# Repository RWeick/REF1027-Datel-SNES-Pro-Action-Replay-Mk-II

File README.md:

# REF1027-Datel-SNES-Pro-Action-Replay-Mk-II
Everything necessary to produce the SNES Pro Action Replay Mk II by Datel

PCB Thickness: 1.0 mm

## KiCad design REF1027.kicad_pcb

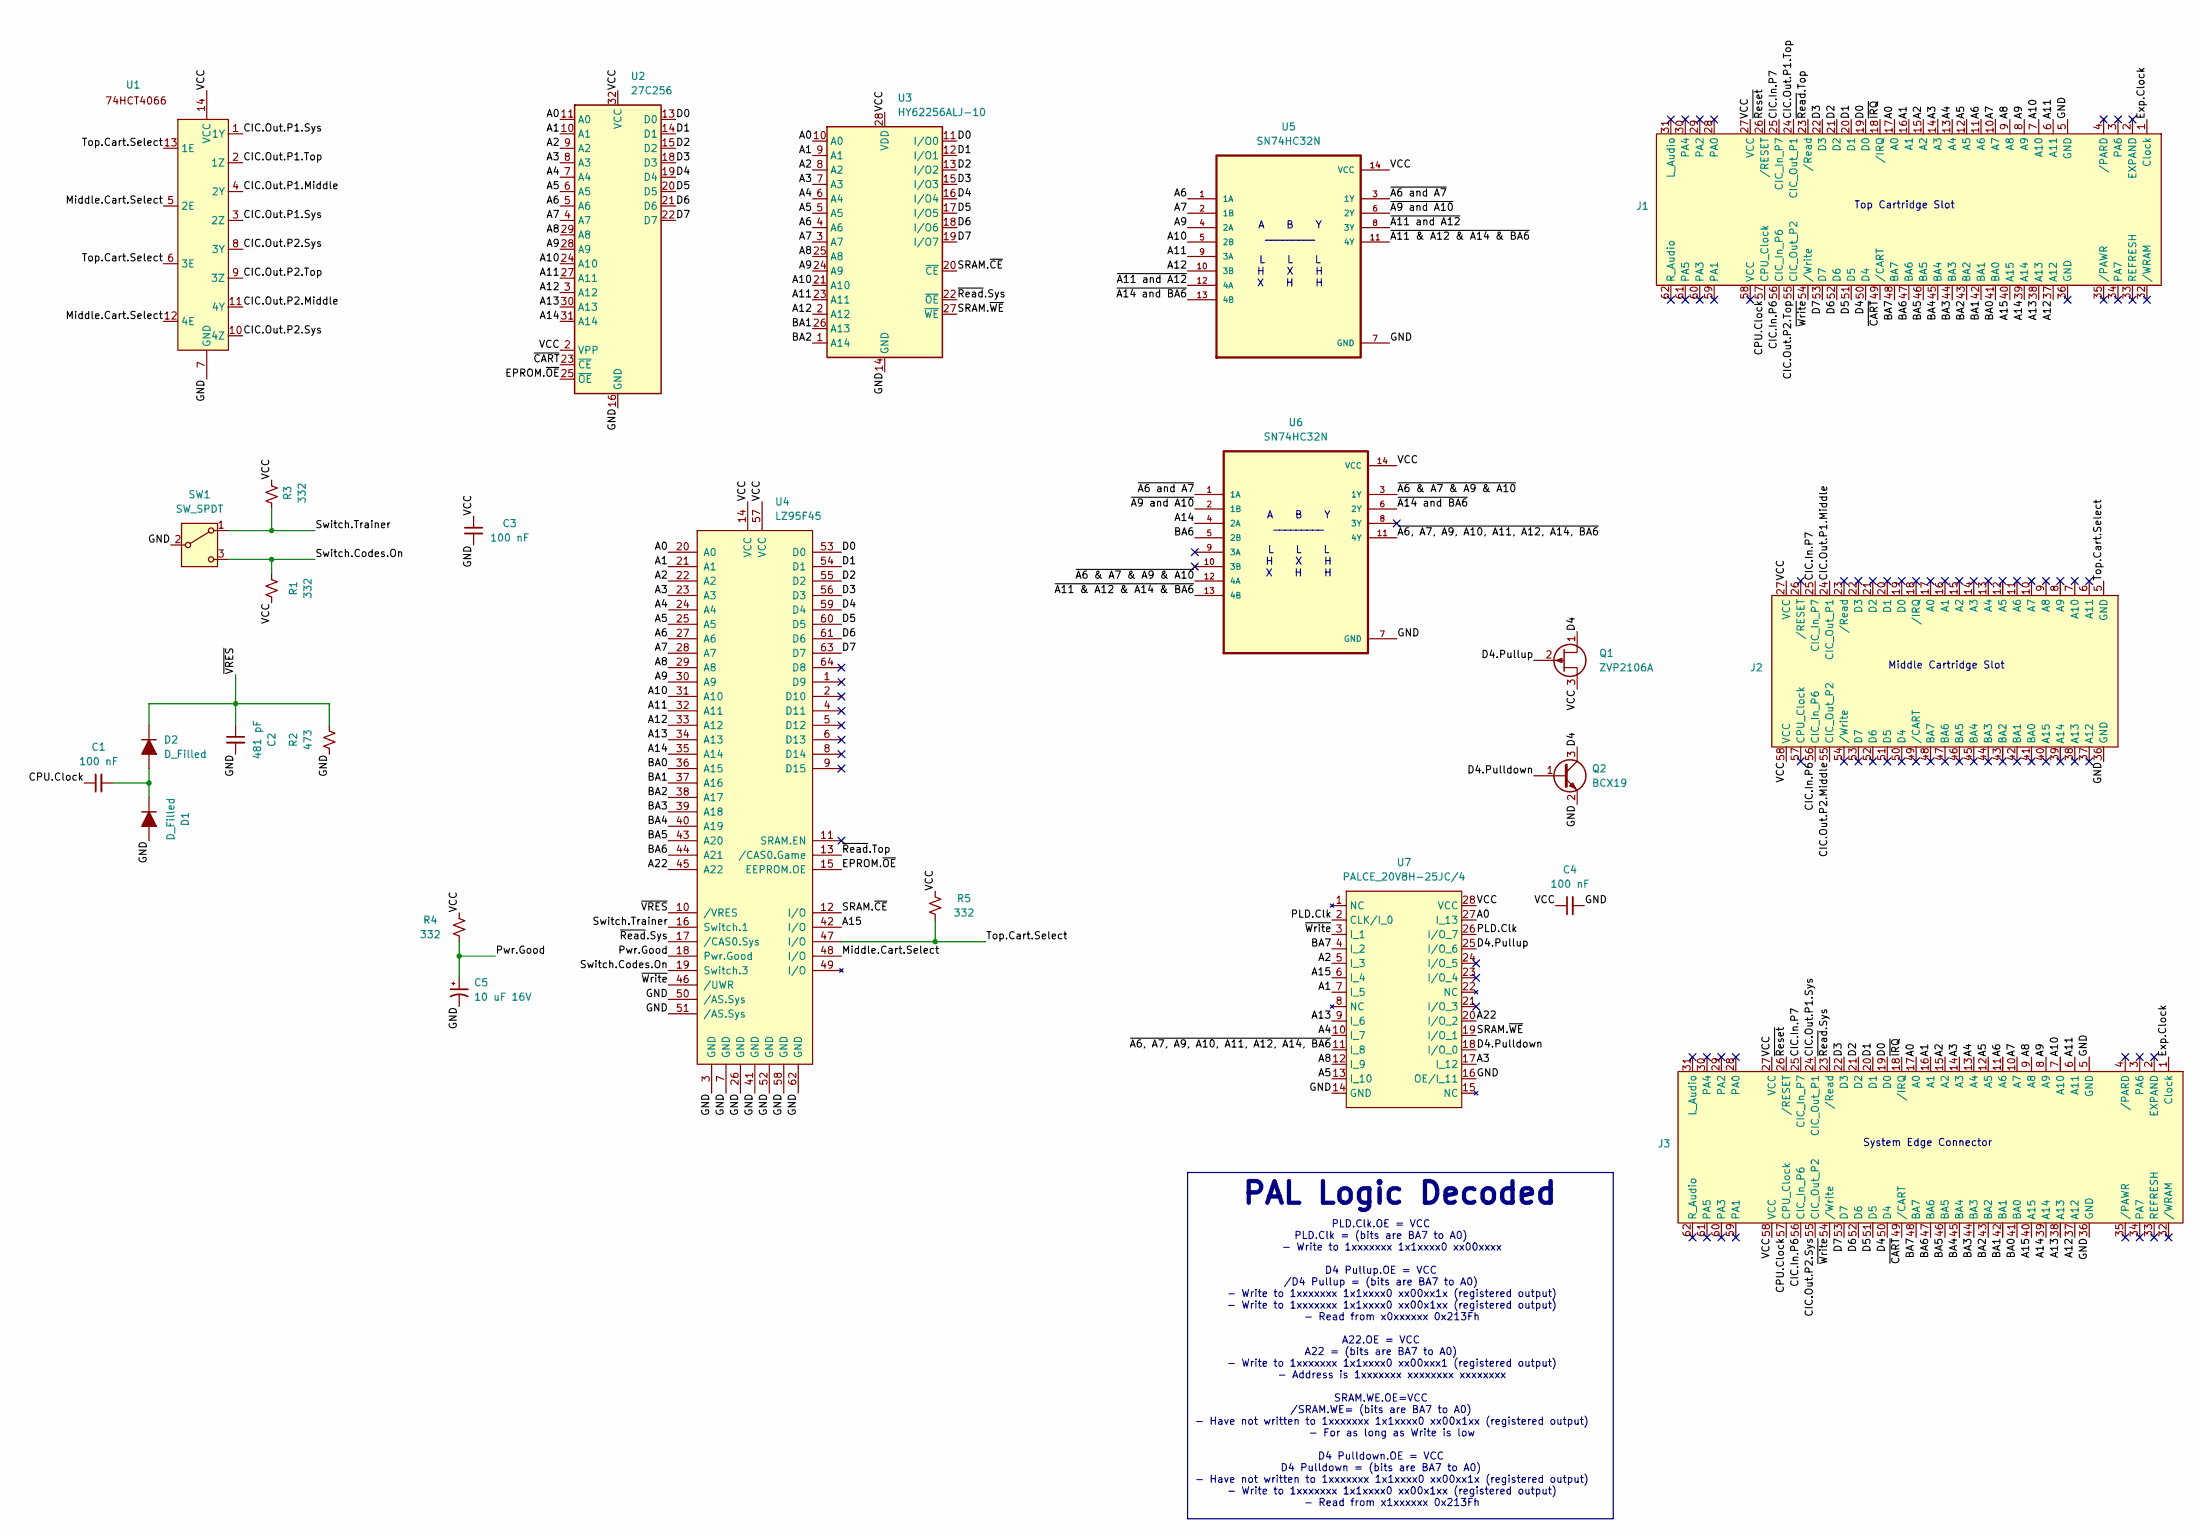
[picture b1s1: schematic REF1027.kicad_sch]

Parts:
C1, C3, C4: 100 nF; Capacitor
C2: 481 pF; Capacitor
C5: 10 uF 16V; CP_Radial_D5.0mm_P2.50mm
D1, D2: D_Filled; Diode
J1: Top Edge Connector
J2: Middle Cartridge Slot
J3: Bottom Edge Connector
Q1: ZVP2106A; TO-92Flat
Q2: BCX19; SOT-23
R1, R3, R4, R5: 332; Resistor
R2: 473; Resistor
SW1: SW_SPDT; Switch
U1: SOIC-14
U2: 27C256
U3: HY62256ALJ-10; HY62256ALJ
U4: LZ95F45
U5, U6: SN74HC32N; SOIC-14
U7: PALCE_20V8H-25JC/4; PALCE20V8H

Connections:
/A0: J1.17 (A0), J3.17 (A0), U2.11 (A0), U3.10 (A0), U4.20 (A0), U7.27 (I_13)
/A1: J1.16 (A1), J3.16 (A1), U2.10 (A1), U3.9 (A1), U4.21 (A1), U7.7 (I_5)
/A2: J1.15 (A2), J3.15 (A2), U2.9 (A2), U3.8 (A2), U4.22 (A2), U7.5 (I_3)
/A3: J1.14 (A3), J3.14 (A3), U2.8 (A3), U3.7 (A3), U4.23 (A3), U7.17 (I_12)
/A4: J1.13 (A4), J3.13 (A4), U2.7 (A4), U3.6 (A4), U4.24 (A4), U7.10 (I_7)
/A5: J1.12 (A5), J3.12 (A5), U2.6 (A5), U3.5 (A5), U4.25 (A5), U7.13 (I_10)
/A6: J1.11 (A6), J3.11 (A6), U2.5 (A6), U3.4 (A6), U4.27 (A6), U5.1 (1A)
/A7: J1.10 (A7), J3.10 (A7), U2.4 (A7), U3.3 (A7), U4.28 (A7), U5.2 (1B)
/A8: J1.9 (A8), J3.9 (A8), U2.29 (A8), U3.25 (A8), U4.29 (A8), U7.12 (I_9)
/A9: J1.8 (A9), J3.8 (A9), U2.28 (A9), U3.24 (A9), U4.30 (A9), U5.4 (2A)
/A10: J1.7 (A10), J3.7 (A10), U2.24 (A10), U3.21 (A10), U4.31 (A10), U5.5 (2B)
/A11: J1.6 (A11), J3.6 (A11), U2.27 (A11), U3.23 (A11), U4.32 (A11), U5.9 (3A)
/A12: J1.37 (A12), J3.37 (A12), U2.3 (A12), U3.2 (A12), U4.33 (A12), U5.10 (3B)
/A13: J1.38 (A13), J3.38 (A13), U2.30 (A13), U4.34 (A13), U7.9 (I_6)
/A14: J1.39 (A14), J3.39 (A14), U2.31 (A14), U4.35 (A14), U6.4 (2A)
/A15: J1.40 (A15), J3.40 (A15), U4.42 (I/O), U7.6 (I_4)
/A22: U4.45 (A22), U7.20 (I/O_2)
/BA0: J1.41 (BA0), J3.41 (BA0), U4.36 (A15)
/BA1: J1.42 (BA1), J3.42 (BA1), U3.26 (A13), U4.37 (A16)
/BA2: J1.43 (BA2), J3.43 (BA2), U3.1 (A14), U4.38 (A17)
/BA3: J1.44 (BA3), J3.44 (BA3), U4.39 (A18)
/BA4: J1.45 (BA4), J3.45 (BA4), U4.40 (A19)
/BA5: J1.46 (BA5), J3.46 (BA5), U4.43 (A20)
/BA6: J1.47 (BA6), J3.47 (BA6), U4.44 (A21), U6.5 (2B)
/BA7: J1.48 (BA7), J3.48 (BA7), U7.4 (I_2)
/CIC.In.P6: J1.56 (CIC_In_P6), J2.56 (CIC_In_P6), J3.56 (CIC_In_P6)
/CIC.In.P7: J1.25 (CIC_In_P7), J2.25 (CIC_In_P7), J3.25 (CIC_In_P7)
/CIC.Out.P1.Middle: J2.24 (CIC_Out_P1), U1.4 (2Y)
/CIC.Out.P1.Sys: J3.24 (CIC_Out_P1), U1.1 (1Y), U1.3 (2Z)
/CIC.Out.P1.Top: J1.24 (CIC_Out_P1), U1.2 (1Z)
/CIC.Out.P2.Middle: J2.55 (CIC_Out_P2), U1.11 (4Y)
/CIC.Out.P2.Sys: J3.55 (CIC_Out_P2), U1.8 (3Y), U1.10 (4Z)
/CIC.Out.P2.Top: J1.55 (CIC_Out_P2), U1.9 (3Z)
/CPU.Clock: C1.1, J1.57 (CPU_Clock), J3.57 (CPU_Clock)
/D0: J1.19 (D0), J3.19 (D0), U2.13 (D0), U3.11 (I/O0), U4.53 (D0)
/D1: J1.20 (D1), J3.20 (D1), U2.14 (D1), U3.12 (I/O1), U4.54 (D1)
/D2: J1.21 (D2), J3.21 (D2), U2.15 (D2), U3.13 (I/O2), U4.55 (D2)
/D3: J1.22 (D3), J3.22 (D3), U2.18 (D3), U3.15 (I/O3), U4.56 (D3)
/D4: J1.50 (D4), J3.50 (D4), Q1.1 (D), Q2.3 (C), U2.19 (D4), U3.16 (I/O4), U4.59 (D4)
/D4.Pulldown: Q2.1 (B), U7.18 (I/O_0)
/D4.Pullup: Q1.2 (G), U7.25 (I/O_6)
/D5: J1.51 (D5), J3.51 (D5), U2.20 (D5), U3.17 (I/O5), U4.60 (D5)
/D6: J1.52 (D6), J3.52 (D6), U2.21 (D6), U3.18 (I/O6), U4.61 (D6)
/D7: J1.53 (D7), J3.53 (D7), U2.22 (D7), U3.19 (I/O7), U4.63 (D7)
/EPROM.~OE: U2.25 (~OE), U4.15 (EEPROM.OE)
/Exp.Clock: J1.1 (Clock), J3.1 (Clock)
/GND: C2.2, C3.2, C4.2, C5.2, D1.2 (A), J1.5 (GND), J2.36 (GND), J3.5 (GND), J3.36 (GND), Q2.2 (E), R2.1, SW1.2 (B), U1.7 (GND), U2.16 (GND), U3.14 (GND), U4.3 (GND), U4.7 (GND), U4.26 (GND), U4.41 (GND), U4.50 (/AS.Sys), U4.51 (/AS.Sys), U4.52 (GND), U4.58 (GND), U4.62 (GND), U5.7 (GND), U6.7 (GND), U7.14 (GND), U7.16 (OE/I_11)
/Middle.Cart.Select: U1.5 (2E), U1.12 (4E), U4.48 (I/O)
/PLD.Clk: U7.2 (CLK/I_0), U7.26 (I/O_7)
/Pwr.Good: C5.1, R4.1, U4.18 (Pwr.Good)
/SRAM.~CE: U3.20 (~CE), U4.12 (I/O)
/SRAM.~WE: U3.27 (~WE), U7.19 (I/O_1)
/Switch.Codes.On: R1.1, SW1.3 (C), U4.19 (Switch.3)
/Switch.Trainer: R3.1, SW1.1 (A), U4.16 (Switch.1)
/Top.Cart.Select: J2.5 (GND), R5.2, U1.6 (3E), U1.13 (1E), U4.47 (I/O)
/VCC: C3.1, C4.1, J1.27 (VCC), J2.27 (VCC), J2.58 (VCC), J3.27 (VCC), J3.58 (VCC), Q1.3 (S), R1.2, R3.2, R4.2, R5.1, U1.14 (VCC), U2.2 (VPP), U2.32 (VCC), U3.28 (VDD), U4.14 (VCC), U4.57 (VCC), U5.14 (VCC), U6.14 (VCC), U7.28 (VCC)
/~A6 & A7 & A9 & A10: U6.3 (1Y), U6.12 (4A)
/~A6 and A7: U5.3 (1Y), U6.1 (1A)
/~A6, A7, A9, A10, A11, A12, A14, BA6: U6.11 (4Y), U7.11 (I_8)
/~A9 and A10: U5.6 (2Y), U6.2 (1B)
/~A11 & A12 & A14 & BA6: U5.11 (4Y), U6.13 (4B)
/~A11 and A12: U5.8 (3Y), U5.12 (4A)
/~A14 and BA6: U5.13 (4B), U6.6 (2Y)
/~CART: J1.49 (/CART), J3.49 (/CART), U2.23 (~CE)
/~IRQ: J1.18 (/IRQ), J3.18 (/IRQ)
/~Read.Sys: J3.23 (/Read), U3.22 (~OE), U4.17 (/CAS0.Sys)
/~Read.Top: J1.23 (/Read), U4.13 (/CAS0.Game)
/~Reset: J1.26 (/RESET), J3.26 (/RESET)
/~VRES: C2.1, D2.1 (K), R2.2, U4.10 (/VRES)
/~Write: J1.54 (/Write), J3.54 (/Write), U4.46 (/UWR), U7.3 (I_1)
unnamed: C1.2, D1.1 (K), D2.2 (A)

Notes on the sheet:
Top Cartridge Slot
A B Y _________ L L L H X H X H H
System Edge Connector
Middle Cartridge Slot
PAL Logic Decoded
PLD.Clk.OE = VCC PLD.Clk = (bits are BA7 to A0) - Write to 1xxxxxxx 1x1xxxx0 xx00xxxx D4 Pullup.OE = VCC /D4 Pullup = (bits are BA7 to A0) - Write to 1xxxxxxx 1x1xxxx0 xx00xx1x (registered output) - Write to 1xxxxxxx 1x1xxxx0 xx00x1xx (registered output) - Read from x0xxxxxx 0x213Fh A22.OE = VCC A2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

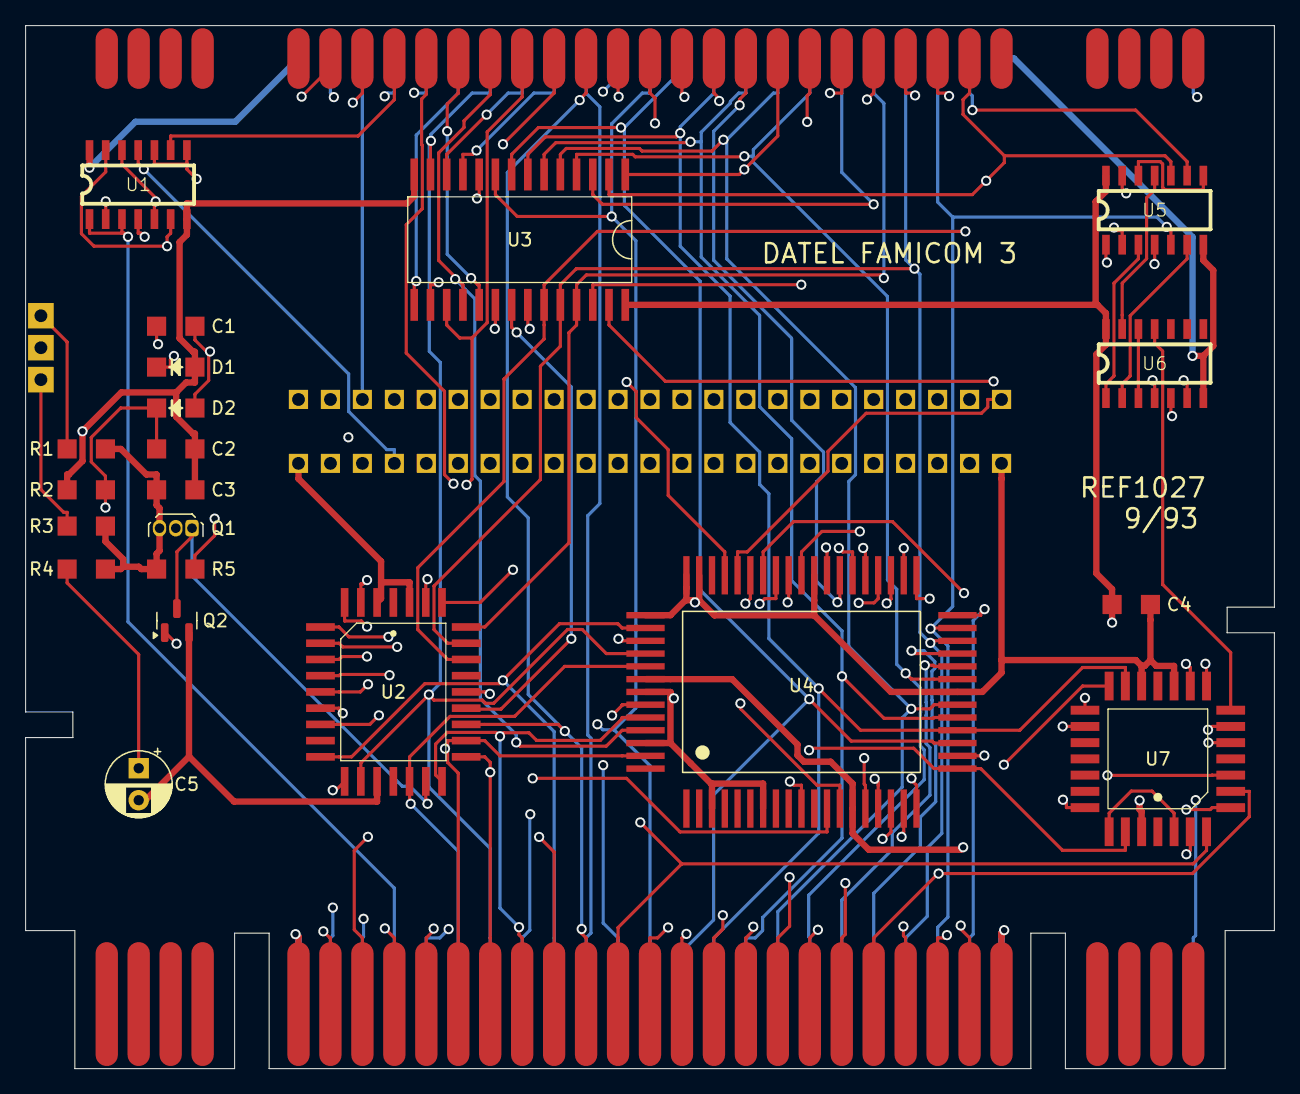
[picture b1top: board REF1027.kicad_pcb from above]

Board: 4 copper layers, 97.7 x 81.6 mm, 25 parts (0 on the bottom side), 71 nets.
